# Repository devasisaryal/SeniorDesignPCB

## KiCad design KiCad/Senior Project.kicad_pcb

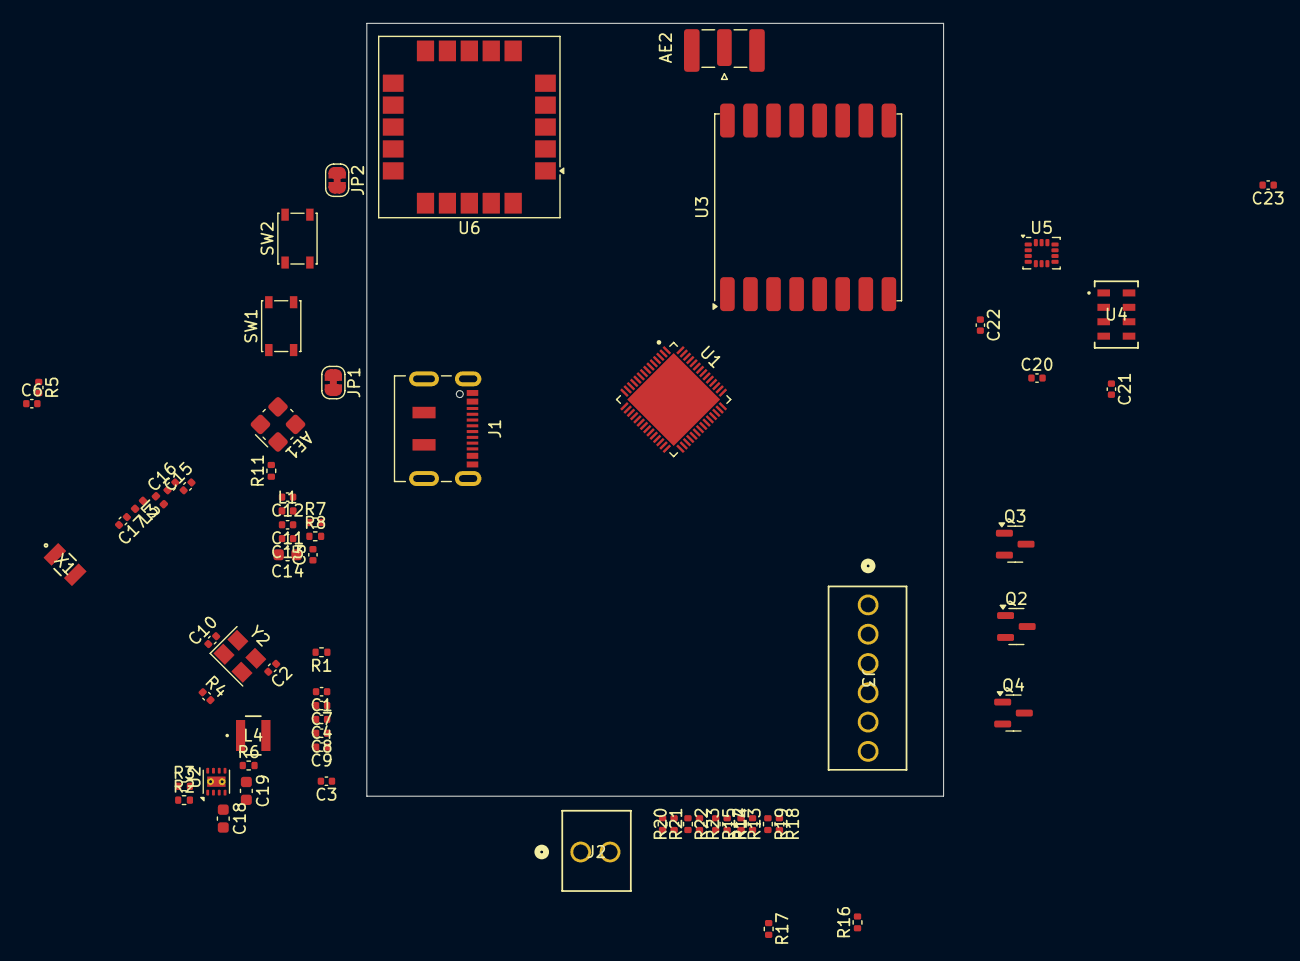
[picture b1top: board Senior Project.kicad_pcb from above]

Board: 4 copper layers, 50.0 x 67.0 mm, 68 parts (0 on the bottom side), 45 nets, no tracks yet.

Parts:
AE1: Antenna_Shield; Molex_47948-0001_2.4Ghz
AE2: Antenna_Shield; SMA_Samtec_SMA-J-P-H-ST-EM1_EdgeMount
C1, C3, C9, C11, C12, C15, C16, C17: 0.1uF; C_0402_1005Metric
C2, C5, C6, C10: TBD; C_0402_1005Metric
C4: 10nF; C_0402_1005Metric
C7, C8, C13: 1uF; C_0402_1005Metric
C14, C18: 10uF; C_0603_1608Metric
C19: 22uF; C_0603_1608Metric
C20, C21, C22, C23: 100nF; C_0402_1005Metric
J1: USB_C_Receptacle_USB2.0_16P; USB_C_Receptacle_JAE_DX07S016JA1R1500
J2: Screw_Terminal_01x02; CONN_OSTVN02A150_OST
J3: Screw_Terminal_01x06; CONN_OSTVN06A150_OST
JP1, JP2: SolderJumper_2_Bridged; SolderJumper-2_P1.3mm_Bridged_RoundedPad1.0x1.5mm
L1, L2, L3: 2.0nH; L_0402_1005Metric
L4: 2.2uH; IND_TAIYO_NR3015_TAY
Q2, Q3, Q4: IRLML0030; SOT-23
R1, R2: 5.1k; R_0402_1005Metric
R3, R6, R11: 100k; R_0402_1005Metric
R4, R5: TBD; C_0402_1005Metric
R7, R8, R13, R15, R17, R19, R21, R23: 10k; R_0402_1005Metric
R12, R16, R20: 470; R_0402_1005Metric
R14, R18, R22: 33k; R_0402_1005Metric
SW1, SW2: SW_Push; SW_SPST_PTS810
U1: ESP32-S3FH4R2; QFN40P700X700X90-57N
U2: TPS62162DSG; WSON-8-1EP_2x2mm_P0.5mm_EP0.9x1.6mm_ThermalVias
U3: RFM95W-868S2; HOPERF_RFM9XW_SMD
U4: MS560702BA03-50; SON8_MS5611_TEC
U5: LSM6DSO32TR; LGA-14_3x2.5mm_P0.5mm_LayoutBorder3x4y
U6: SAM-M8Q; ublox_SAM-M8Q
X1: FC-135 32.7680KA-A5; XTAL_FC-135_EPS
Y2: Crystal_GND23; Crystal_SMD_3225-4Pin_3.2x2.5mm

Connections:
+3V3: C1.1, C4.1, C8.1, C9.1, C12.1, C13.1, C14.1, C19.1, C20.1, C21.1, C22.1, C23.2, L1.2, L4.2, R3.2, R6.1, R7.1, R8.1, R11.1, U1.20 (VDD3P3_RTC), U1.46 (VDD3P3_CPU), U1.55 (VDDA), U1.56 (VDDA__1), U2.6 (VOS), U3.13 (3.3V), U4.1 (VDD), U4.2 (PS), U4.4 (~CSB), U5.5 (VDDIO), U5.8 (VDD), U5.12 (CS), U6.2 (VCC_IO), U6.17 (VCC)
+BATT: C18.1, J2.2, J3.1, J3.3, J3.5, U2.2 (VIN), U2.3 (EN)
/ESP-32 Power Coupler/VDD3P3: C11.1, L1.1, U1.2 (VDD3P3), U1.3 (VDD3P3__1)
/FSPICLK: U1.17 (GPIO12), U3.4 (SCK)
/FSPICS0: U1.15 (GPIO10), U3.5 (NSS)
/FSPID: U1.16 (GPIO11), U3.3 (MOSI)
/FSPIQ: U1.18 (GPIO13), U3.2 (MISO)
/Interrupt: U1.6 (GPIO1), U3.14 (DIO0)
/LNA Shield/LNA_IN: C15.1, L2.1, U1.1 (LNA_IN)
/PowerReg/PG: R6.2, U2.8 (PG)
/Pyro Channel1/Pyro Pin: J3.2, Q2.3 (D), R14.1
/Pyro Channel2/Pyro Pin: J3.4, Q3.3 (D), R18.1
/Pyro Channel3/Pyro Pin: J3.6, Q4.3 (D), R22.1
/Pyro GPIO 1: R12.1, U1.43 (GPIO38)
/Pyro GPIO 2: R16.1, U1.36 (GPIO48/SPICLK_N)
/Pyro GPIO 3: R20.1, U1.37 (GPIO47/SPICLK_P)
/RADIO_RST: U1.9 (GPIO4), U3.6 (RESET)
/SCL: R8.2, U1.14 (GPIO9), U4.8 (SCLK), U5.13 (SCL), U6.12 (SCL)
/SDA: R7.2, U1.13 (GPIO8), U4.7 (SDI/SDA), U5.14 (SDA), U6.9 (SDA)
/Sense 1: R14.2, R15.1, U1.19 (GPIO14)
/Sense 2: R18.2, R19.1, U1.23 (GPIO17)
/Sense 3: R22.2, R23.1, U1.24 (GPIO18)
/USB_D+: J1.A6 (D+), J1.B6 (D+), R3.1, U1.26 (GPIO20)
/USB_D-: J1.A7 (D-), J1.B7 (D-), U1.25 (GPIO19)
GND: AE2.2 (Shield), C1.2, C2.1, C3.2, C4.2, C5.2, C6.2, C7.2, C8.2, C9.2, C10.2, C11.2, C12.2, C13.2, C14.2, C15.2, C16.2, C17.2, C18.2, C19.2, C20.2, C21.2, C22.2, C23.1, J1.A1 (GND), J1.A12 (GND), J1.B1 (GND), J1.B12 (GND), J1.S1 (SHIELD), J2.1, Q2.2 (S), Q3.2 (S), Q4.2 (S), R1.2, R2.2, R13.2, R15.2, R17.2, R19.2, R21.2, R23.2, SW1.1, SW2.1, U1.57 (GND), U2.1 (PGND), U2.4 (AGND), U2.5 (FB), U2.9 (PAD), U3.1 (GND), U3.8 (GND), U3.10 (GND), U4.3 (GND), U4.5 (~CSB__1), U5.1 (SDO/SA0), U5.2 (SDX), U5.3 (SCX), U5.6 (GND), U5.7 (GND__1), U6.1 (GND), U6.4 (GND), U6.5 (GND), U6.6 (GND), U6.10 (GND), U6.11 (GND), U6.15 (GND), U6.16 (GND), U6.20 (GND), Y2.2, Y2.4
unnamed: AE1.1 (A), C16.1, L2.2, L3.1
unnamed: AE2.1 (A), U3.9 (ANT)
unnamed: C10.1, R4.2, Y2.1
unnamed: C17.1, L3.2
unnamed: J1.A4 (VBUS), J1.A9 (VBUS), J1.B4 (VBUS), J1.B9 (VBUS)
unnamed: J1.A5 (CC1), R1.1
unnamed: J1.B5 (CC2), R2.1
unnamed: JP1.1 (A), SW1.2
unnamed: JP1.2 (B), R11.2, U1.4 (CHIP_PU)
unnamed: JP2.1 (A), SW2.2
unnamed: JP2.2 (B), U1.5 (GPIO0)
unnamed: Q2.1 (G), R12.2, R13.1
unnamed: Q3.1 (G), R16.2, R17.1
unnamed: Q4.1 (G), R20.2, R21.1
unnamed: C3.1, C7.1, U1.29 (VDD_SPI)
unnamed: C6.1, R5.2, U1.22 (XTAL_32K_N), X1.2
unnamed: C5.1, R5.1, U1.21 (XTAL_32K_P), X1.1
unnamed: C2.2, U1.53 (XTAL_N), Y2.3
unnamed: R4.1, U1.54 (XTAL_P)
unnamed: L4.1, U2.7 (SW)

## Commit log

2025-03-31 PCB update
2025-03-31 ERC fixes
2025-03-31 Added diode footprint
2025-03-31 Fixes
2025-04-01 Added the diode changes
2025-04-01 removed traces
